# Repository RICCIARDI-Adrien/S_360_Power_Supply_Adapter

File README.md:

# S-360-xx power supply adapter

Add 4 10-A 2.5x5.5mm jack outputs and a 240V IEC connector with a switch to S-360-5 and S-360-12 AC/DC power supplies.

## Bill of materials

### Electronic parts

| Description | Reference | Amount |
| ----------- | --------- | ------ |
| IEC connector with integrated switch | DC11.0001.007 | 1 |
| 2.5X5.5mm power connector jack | PJ-082BH | 4 |

### Mechanical parts

| Description | Reference | Amount | Description |
| ----------- | --------- | ------ | ----------- |
| 40mm M4 steel hex standoff | 970400471 | 5 | Between upper plate and lower plate |
| 25mm M4 steel screw | - | 4 | Hold PCB |
| 10mm M4 steel screw | - | 14 | Fix upper plate to hex standoffs (5 screws), fix lower plate to hex standoffs (5 screws), fix power supply to lower plate (4 screws) |
| 16mm M3 steel screw | - | 4 | Fix IEC connector to upper plate |
| M4 steel nut | - | 12 | Hold PCB |
| M3 steel nut | - | 2 | Fix IEC connector to upper plate |
| 10mm M4 steel washer | - | 30 | Lock upper plate to hex standoffs (5 washers), lock lower plate to hex standoffs (5 washers), lock power supply to lower plate (4 washers), 4 per PCB screw (16 washers) |
| M3 steel washer | - | 2 | Lock IEC connector to upper plate |

## Documentation

The power supply drawing, found [here](https://fr.aliexpress.com/item/32713332357.html).

## Photo gallery

### PCB

### Casing plates

### Assembly

### Powering a test bench at BayLibre

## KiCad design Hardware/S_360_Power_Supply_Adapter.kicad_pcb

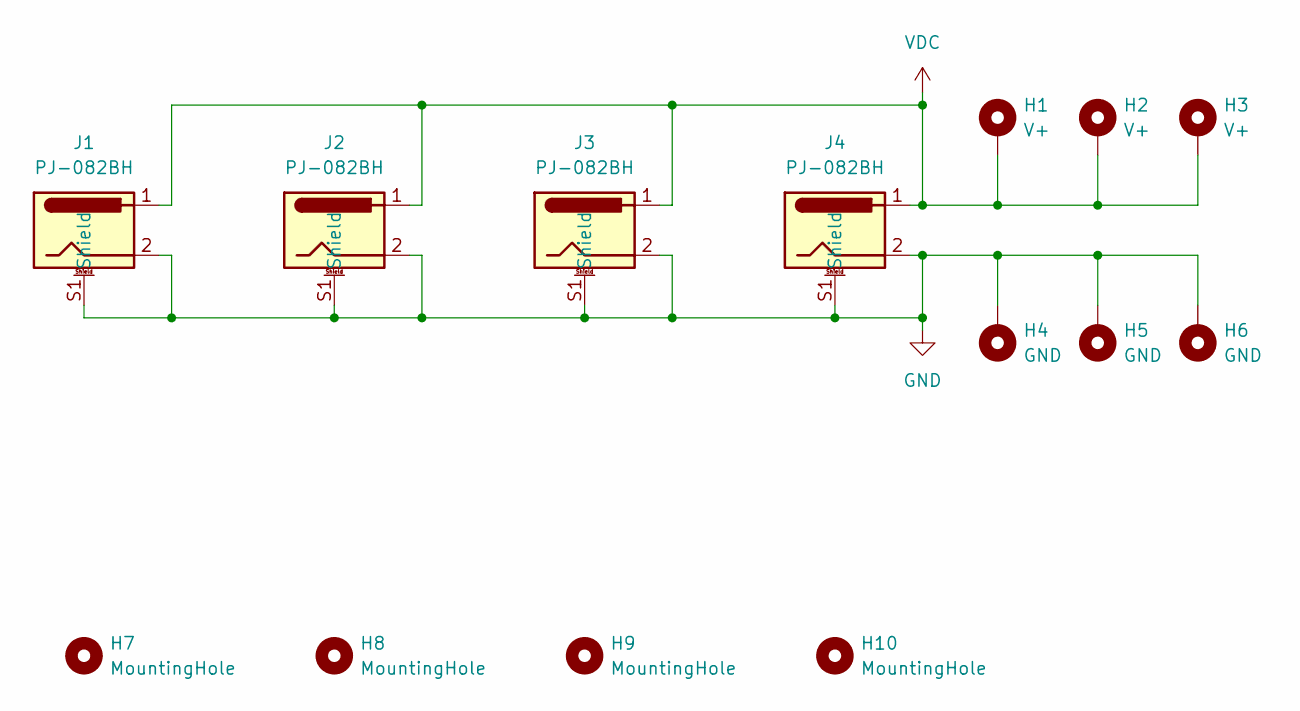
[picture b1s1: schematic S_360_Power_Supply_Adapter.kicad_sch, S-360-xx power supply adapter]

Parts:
H1, H2, H3: V+; MountingHole_4.5mm_Pad_Via
H4, H5, H6: GND; MountingHole_4.5mm_Pad_Via
H7, H8, H9, H10: MountingHole; MountingHole_4.5mm
J1, J2, J3, J4: PJ-082BH

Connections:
GND: H4.1, H5.1, H6.1, J1.2, J1.S1 (Shield), J1.S2 (Shield), J1.S3 (Shield), J1.S4 (Shield), J2.2, J2.S1 (Shield), J2.S2 (Shield), J2.S3 (Shield), J2.S4 (Shield), J3.2, J3.S1 (Shield), J3.S2 (Shield), J3.S3 (Shield), J3.S4 (Shield), J4.2, J4.S1 (Shield), J4.S2 (Shield), J4.S3 (Shield), J4.S4 (Shield)
VDC: H1.1, H2.1, H3.1, J1.1, J2.1, J3.1, J4.1

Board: 2 copper layers, 14 parts (0 on the bottom side), 2 nets, no tracks yet.

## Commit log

2022-11-24 Initial commit. Added README.md with the power supply drawing picture.
2022-11-24 Added MIT license.
2022-11-24 Started casing modeling. Created the power supply block with its fastening holes.
2022-11-25 Added an empty KiCad project for the PCB.
2022-11-25 Added PJ-082BH barrel jack symbol, footprint and 3D model to PCB.
2022-11-25 Finished PCB schematic.
2022-11-25 Finished PCB routing.
2022-11-25 Started casing lower plate design. Also imported the IEC connector and PCB 3D models to the casing.
2022-11-25 Positioned the PCB on the casing lower plate.
2022-11-25 Added all casing lower plate fixation holes and all hex standoffs.
2022-11-25 Started casing upper case. Removed the hex standoff in front of the power supply screw terminal to make screwing cables easier.
2022-11-25 Finished casing upper plate.
2022-11-25 Added a techdraw projection of the casing plates so they can easily be exported to DXF.
2022-11-28 Fixed the IEC connector fixation screw holes that could not be cut by a laser if the plate width was 3mm (there was too little margin between the hole and the connector cut).
2022-11-29 Added more clearance around PCB mounting holes so a nut or a washer can't scratch the mask and touch the copper, creating a short circuit.
2022-12-13 Added electronic and mechanical bill of material to README.md.
2022-12-16 Added pictures to README.md.
2022-12-19 Added more pictures to the README.md.
2023-01-08 Made longer power supply fixation holes on the casing lower plate to accomodate with power supplies poor manufacturing tolerances.
2023-01-26 Made longer and larger power supply fixation holes on the casing lower plate to accomodate with power supplies poor manufacturing tolerances.
